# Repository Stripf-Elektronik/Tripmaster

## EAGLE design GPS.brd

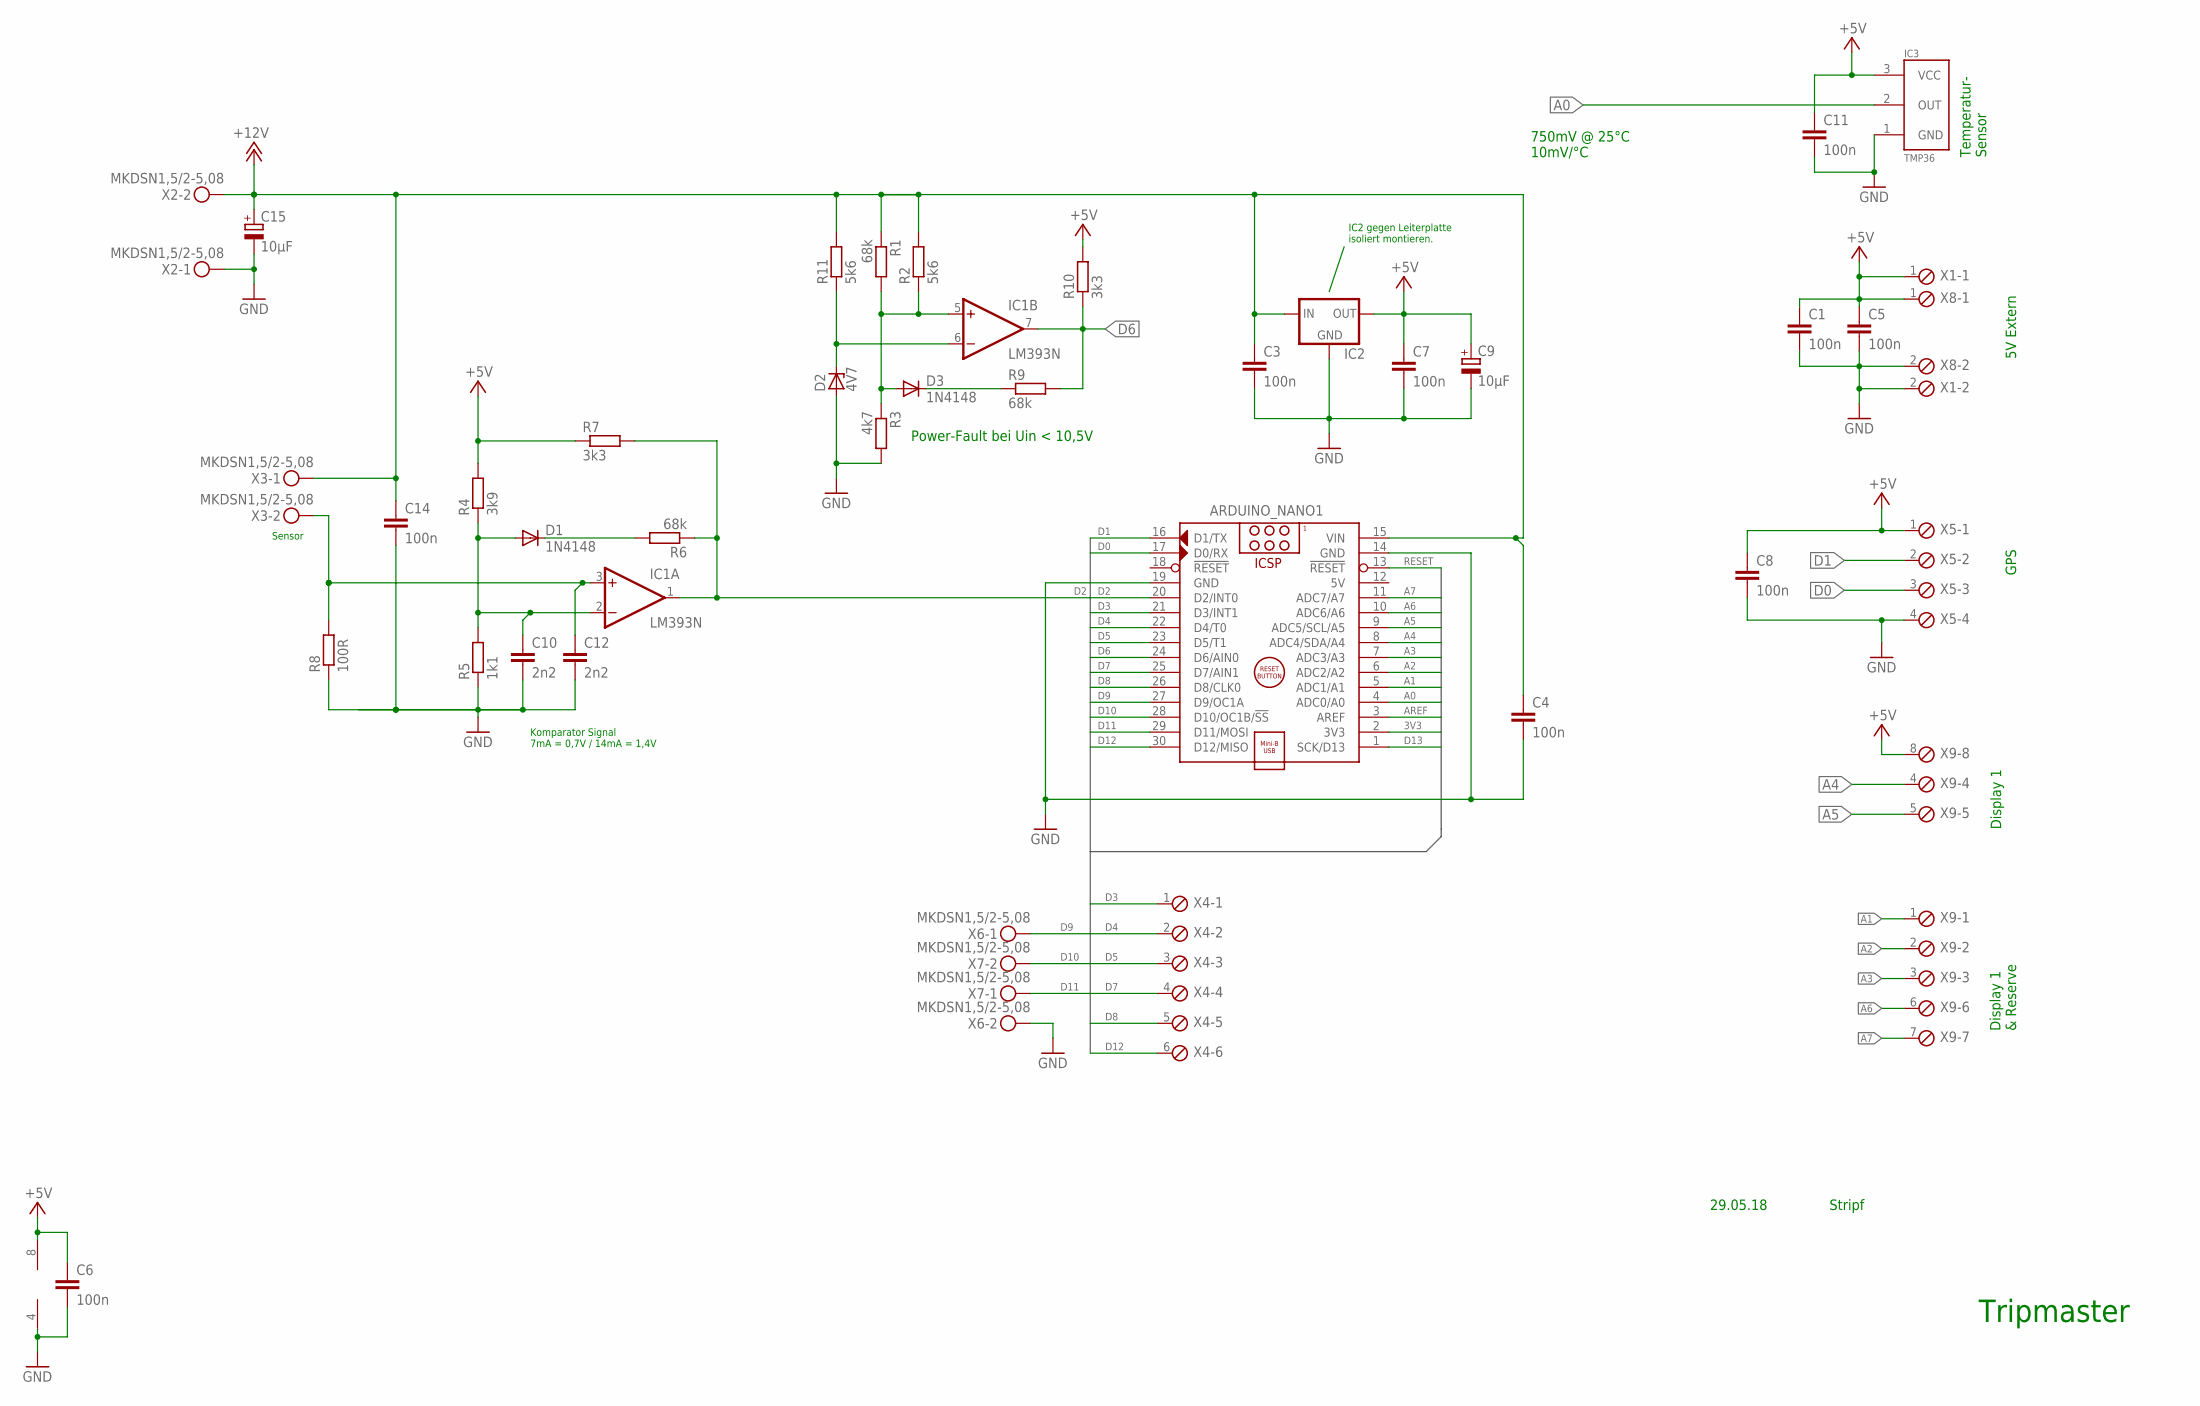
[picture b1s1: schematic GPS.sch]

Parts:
ARDUINO_NANO1: ARDUINO_NANO
C1, C3, C4, C5, C6, C7, C8, C11, C14: 100n; C025-030X050
C9, C15: 10µF; E2,5-6
C10, C12: 2n2; C025-030X050
D1, D3: 1N4148; DO35-7
D2: 4V7; ZDIO-2.5
IC1: LM393N; DIL08
IC2: 78XXL
IC3: TMP36; TO92-LINE
R1, R6, R9: 68k; 0207/2V
R2, R11: 5k6; 0207/2V
R3: 4k7; 0207/2V
R4: 3k9; 0207/2V
R5: 1k1; 0207/2V
R7, R10: 3k3; 0207/2V
R8: 100R; 0207/2V
X1, X8: MPT2; 2POL254
X2, X3, X6, X7: MKDSN1,5/2-5,08
X4: MPT6; 6POL254
X5: MPT4; 4POL254
X9: MPT8; 8POL254

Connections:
3V3: ARDUINO_NANO1.2 (3V3)
5V: ARDUINO_NANO1.12 (5V)
+5V: C1.1, C5.1, C6.1, C7.1, C8.1, C9.+, C11.1, IC1.8 (V+), IC2.OUT, IC3.3 (VCC), R4.2, R7.1, R10.2, X1.1, X5.1, X8.1, X9.8
+12V: ARDUINO_NANO1.15 (VIN), C3.1, C4.1, C14.1, C15.+, IC2.IN, R1.1, R2.2, R11.2, X2.2, X3.1
A0: ARDUINO_NANO1.4 (ADC0/A0), IC3.2 (OUT)
A1: ARDUINO_NANO1.5 (ADC1/A1), X9.1
A2: ARDUINO_NANO1.6 (ADC2/A2), X9.2
A3: ARDUINO_NANO1.7 (ADC3/A3), X9.3
A4: ARDUINO_NANO1.8 (ADC4/SDA/A4), X9.4
A5: ARDUINO_NANO1.9 (ADC5/SCL/A5), X9.5
A6: ARDUINO_NANO1.10 (ADC6/A6), X9.6
A7: ARDUINO_NANO1.11 (ADC7/A7), X9.7
AREF: ARDUINO_NANO1.3 (AREF)
D0: ARDUINO_NANO1.17 (D0/RX), X5.3
D1: ARDUINO_NANO1.16 (D1/TX), X5.2
D2: ARDUINO_NANO1.20 (D2/INT0), IC1.1 (OUT), R6.1, R7.2
D3: ARDUINO_NANO1.21 (D3/INT1), X4.1
D4: ARDUINO_NANO1.22 (D4/T0), X4.2
D5: ARDUINO_NANO1.23 (D5/T1), X4.3
D6: ARDUINO_NANO1.24 (D6/AIN0), IC1.7 (OUT), R9.2, R10.1
D7: ARDUINO_NANO1.25 (D7/AIN1), X4.4
D8: ARDUINO_NANO1.26 (D8/CLK0), X4.5
D9: ARDUINO_NANO1.27 (D9/OC1A), X6.1
D10: ARDUINO_NANO1.28 (D10/OC1B/!SS), X7.2
D11: ARDUINO_NANO1.29 (D11/MOSI), X7.1
D12: ARDUINO_NANO1.30 (D12/MISO), X4.6
D13: ARDUINO_NANO1.1 (SCK/D13)
GND: ARDUINO_NANO1.14 (GND), ARDUINO_NANO1.19 (GND), C1.2, C3.2, C4.2, C5.2, C6.2, C7.2, C8.2, C9.-, C10.2, C11.2, C12.2, C14.2, C15.-, D2.A, IC1.4 (V-), IC2.GND, IC3.1 (GND), R3.2, R5.1, R8.1, X1.2, X2.1, X5.4, X6.2, X8.2
unnamed: D3.A, IC1.5 (+IN), R1.2, R2.1, R3.1
unnamed: D3.C, R9.1
unnamed: D2.C, IC1.6 (-IN), R11.1
unnamed: D1.C, R6.2
unnamed: C10.1, D1.A, IC1.2 (-IN), R4.1, R5.2
unnamed: C12.1, IC1.3 (+IN), R8.2, X3.2
RESET: ARDUINO_NANO1.13 (!RESET)

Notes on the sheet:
Sensor
Komparator Signal 7mA = 0,7V / 14mA = 1,4V
Power-Fault bei Uin < 10,5V
Display 1
GPS
Temperatur- Sensor
Tripmaster
5V Extern
750mV @ 25°C 10mV/°C
Display 1 & Reserve
29.05.18
Stripf
IC2 gegen Leiterplatte isoliert montieren.

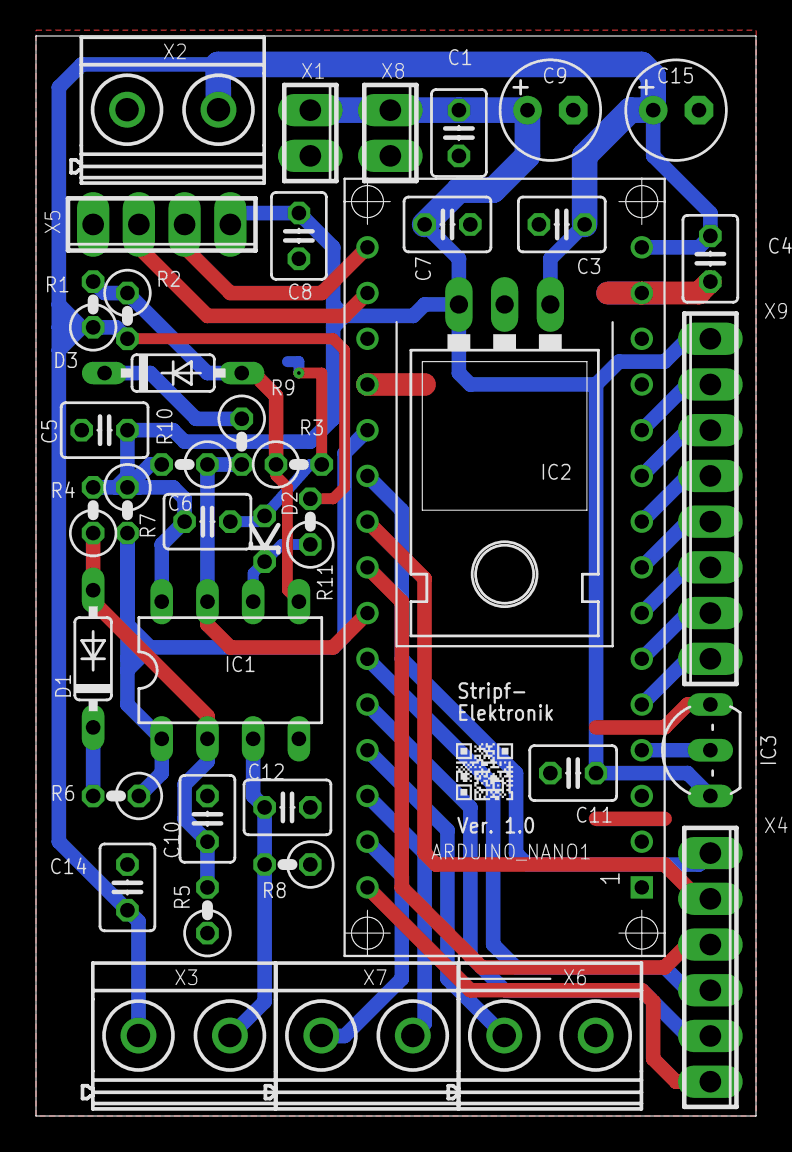
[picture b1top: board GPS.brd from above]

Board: 2 copper layers, 40.0 x 60.0 mm, 42 parts (0 on the bottom side), 30 nets.

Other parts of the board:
U$1: QR-CODE-SMALL
U$3: GLIMMER_TO220

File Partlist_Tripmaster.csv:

"Part";"Value";"Device";"Package";"Library";"Description";"Side";"InchX";"InchY";"mmX";"mmY";"Angle";"MF";"MPN";"OC_FARNELL";"OC_NEWARK";
"ARDUINO_NANO1";"";"ARDUINO_NANO";"ARDUINO_NANO";"ArduinoNanoV30";"Arduino Nano V3.0 Module";"CS";"    1.0250";"    1.3000";"   26.0350";"   33.0200";"  90.00";"";"";"";"";
"C1";"100n";"C-EU025-030X050";"C025-030X050";"rcl";"CAPACITOR, European symbol";"CS";"    0.9250";"    2.1500";"   23.4950";"   54.6100";" 270.00";"";"";"";"";
"C3";"100n";"C-EU025-030X050";"C025-030X050";"rcl";"CAPACITOR, European symbol";"CS";"    1.1500";"    1.9500";"   29.2100";"   49.5300";" 180.00";"";"";"";"";
"C4";"100n";"C-EU025-030X050";"C025-030X050";"rcl";"CAPACITOR, European symbol";"CS";"    1.4750";"    1.8750";"   37.4650";"   47.6250";" 270.00";"";"";"";"";
"C5";"100n";"C-EU025-030X050";"C025-030X050";"rcl";"CAPACITOR, European symbol";"CS";"    0.1500";"    1.5000";"    3.8100";"   38.1000";" 180.00";"";"";"";"";
"C6";"100n";"C-EU025-030X050";"C025-030X050";"rcl";"CAPACITOR, European symbol";"CS";"    0.3750";"    1.3000";"    9.5250";"   33.0200";"   0.00";"";"";"";"";
"C7";"100n";"C-EU025-030X050";"C025-030X050";"rcl";"CAPACITOR, European symbol";"CS";"    0.9000";"    1.9500";"   22.8600";"   49.5300";"   0.00";"";"";"";"";
"C8";"100n";"C-EU025-030X050";"C025-030X050";"rcl";"CAPACITOR, European symbol";"CS";"    0.5750";"    1.9250";"   14.6050";"   48.8950";" 270.00";"";"";"";"";
"C9";"10µF";"CPOL-EUE2.5-6";"E2,5-6";"rcl";"POLARIZED CAPACITOR, European symbol";"CS";"    1.1250";"    2.2000";"   28.5750";"   55.8800";"   0.00";"";"";"";"";
"C10";"2n2";"C-EU025-030X050";"C025-030X050";"rcl";"CAPACITOR, European symbol";"CS";"    0.3750";"    0.6500";"    9.5250";"   16.5100";"  90.00";"";"";"";"";
"C11";"100n";"C-EU025-030X050";"C025-030X050";"rcl";"CAPACITOR, European symbol";"CS";"    1.1750";"    0.7500";"   29.8450";"   19.0500";" 180.00";"";"";"";"";
"C12";"2n2";"C-EU025-030X050";"C025-030X050";"rcl";"CAPACITOR, European symbol";"CS";"    0.5500";"    0.6750";"   13.9700";"   17.1450";"   0.00";"";"";"";"";
"C14";"100n";"C-EU025-030X050";"C025-030X050";"rcl";"CAPACITOR, European symbol";"CS";"    0.2000";"    0.5000";"    5.0800";"   12.7000";"  90.00";"";"";"";"";
"C15";"10µF";"CPOL-EUE2.5-6";"E2,5-6";"rcl";"POLARIZED CAPACITOR, European symbol";"CS";"    1.4000";"    2.2000";"   35.5600";"   55.8800";"   0.00";"";"";"";"";
"D1";"1N4148";"1N4148DO35-7";"DO35-7";"diode";"DIODE";"CS";"    0.1250";"    1.0000";"    3.1750";"   25.4000";"  90.00";"";"";"";"";
"D2";"4V7";"ZENER-DIODEZD-2.5";"ZDIO-2.5";"diode";"Z-Diode";"CS";"    0.5000";"    1.2625";"   12.7000";"   32.0675";"  90.00";"";"";"";"";
"D3";"1N4148";"1N4148DO35-7";"DO35-7";"diode";"DIODE";"CS";"    0.3000";"    1.6250";"    7.6200";"   41.2750";"   0.00";"";"";"";"";
"IC1";"LM393N";"LM393N";"DIL08";"linear2";"COMPARATOR";"CS";"    0.4250";"    0.9750";"   10.7950";"   24.7650";"   0.00";"";"";"";"";
"IC2";"";"78XXL";"78XXL";"v-reg";"VOLTAGE REGULATOR";"CS";"    1.0250";"    1.6250";"   26.0350";"   41.2750";" 180.00";"";"";"";"";
"IC3";"TMP36";"TMP36";"TO92-LINE";"Stripf";"";"CS";"    1.4750";"    0.8000";"   37.4650";"   20.3200";"  90.00";"";"";"";"";
"R1";"68k";"R-EU_0207/2V";"0207/2V";"rcl";"RESISTOR, European symbol";"CS";"    0.1250";"    1.7750";"    3.1750";"   45.0850";"  90.00";"";"";"";"";
"R2";"5k6";"R-EU_0207/2V";"0207/2V";"rcl";"RESISTOR, European symbol";"CS";"    0.2000";"    1.7500";"    5.0800";"   44.4500";" 270.00";"";"";"";"";
"R3";"4k7";"R-EU_0207/2V";"0207/2V";"rcl";"RESISTOR, European symbol";"CS";"    0.5750";"    1.4250";"   14.6050";"   36.1950";"   0.00";"";"";"";"";
"R4";"3k9";"R-EU_0207/2V";"0207/2V";"rcl";"RESISTOR, European symbol";"CS";"    0.1250";"    1.3250";"    3.1750";"   33.6550";"  90.00";"";"";"";"";
"R5";"1k1";"R-EU_0207/2V";"0207/2V";"rcl";"RESISTOR, European symbol";"CS";"    0.3750";"    0.4500";"    9.5250";"   11.4300";"  90.00";"";"";"";"";
"R6";"68k";"R-EU_0207/2V";"0207/2V";"rcl";"RESISTOR, European symbol";"CS";"    0.1750";"    0.7000";"    4.4450";"   17.7800";" 180.00";"";"";"";"";
"R7";"3k3";"R-EU_0207/2V";"0207/2V";"rcl";"RESISTOR, European symbol";"CS";"    0.2000";"    1.3250";"    5.0800";"   33.6550";" 270.00";"";"";"";"";
"R8";"100R";"R-EU_0207/2V";"0207/2V";"rcl";"RESISTOR, European symbol";"CS";"    0.5500";"    0.5500";"   13.9700";"   13.9700";" 180.00";"";"";"";"";
"R9";"68k";"R-EU_0207/2V";"0207/2V";"rcl";"RESISTOR, European symbol";"CS";"    0.4500";"    1.4750";"   11.4300";"   37.4650";" 270.00";"";"";"";"";
"R10";"3k3";"R-EU_0207/2V";"0207/2V";"rcl";"RESISTOR, European symbol";"CS";"    0.3250";"    1.4250";"    8.2550";"   36.1950";" 180.00";"";"";"";"";
"R11";"5k6";"R-EU_0207/2V";"0207/2V";"rcl";"RESISTOR, European symbol";"CS";"    0.6000";"    1.3000";"   15.2400";"   33.0200";"  90.00";"";"";"";"";
"X1";"";"MPT2";"2POL254";"con-phoenix-254";"PHOENIX CONNECTOR";"CS";"    0.6000";"    2.1500";"   15.2400";"   54.6100";" 270.00";"";"";"unknown";"unknown";
"X2";"MKDSN1,5/2-5,08";"MKDSN1,5/2-5,08";"MKDSN1,5/2-5,08";"con-phoenix-508";"MKDSN 1,5/ 2-5,08 Printklemme";"CS";"    0.3000";"    2.2000";"    7.6200";"   55.8800";"   0.00";"";"";"";"";
"X3";"MKDSN1,5/2-5,08";"MKDSN1,5/2-5,08";"MKDSN1,5/2-5,08";"con-phoenix-508";"MKDSN 1,5/ 2-5,08 Printklemme";"CS";"    0.3250";"    0.1750";"    8.2550";"    4.4450";"   0.00";"";"";"";"";
"X4";"";"MPT6";"6POL254";"con-phoenix-254";"PHOENIX CONNECTOR";"CS";"    1.4750";"    0.3250";"   37.4650";"    8.2550";" 270.00";"";"";"unknown";"unknown";
"X5";"";"MPT4";"4POL254";"con-phoenix-254";"PHOENIX CONNECTOR";"CS";"    0.2750";"    1.9500";"    6.9850";"   49.5300";" 180.00";"";"";"unknown";"unknown";
"X6";"MKDSN1,5/2-5,08";"MKDSN1,5/2-5,08";"MKDSN1,5/2-5,08";"con-phoenix-508";"MKDSN 1,5/ 2-5,08 Printklemme";"CS";"    1.1250";"    0.1750";"   28.5750";"    4.4450";"   0.00";"";"";"";"";
"X7";"MKDSN1,5/2-5,08";"MKDSN1,5/2-5,08";"MKDSN1,5/2-5,08";"con-phoenix-508";"MKDSN 1,5/ 2-5,08 Printklemme";"CS";"    0.7250";"    0.1750";"   18.4150";"    4.4450";"   0.00";"";"";"";"";
"X8";"";"MPT2";"2POL254";"con-phoenix-254";"PHOENIX CONNECTOR";"CS";"    0.7750";"    2.1500";"   19.6850";"   54.6100";" 270.00";"";"";"unknown";"unknown";
"X9";"";"MPT8";"8POL254";"con-phoenix-254";"PHOENIX CONNECTOR";"CS";"    1.4750";"    1.3500";"   37.4650";"   34.2900";"  90.00";"";"";"unknown";"unknown";

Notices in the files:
parts and their libraries:
Stripf_: Alle Rechte vorbehalten - All rights reserved
